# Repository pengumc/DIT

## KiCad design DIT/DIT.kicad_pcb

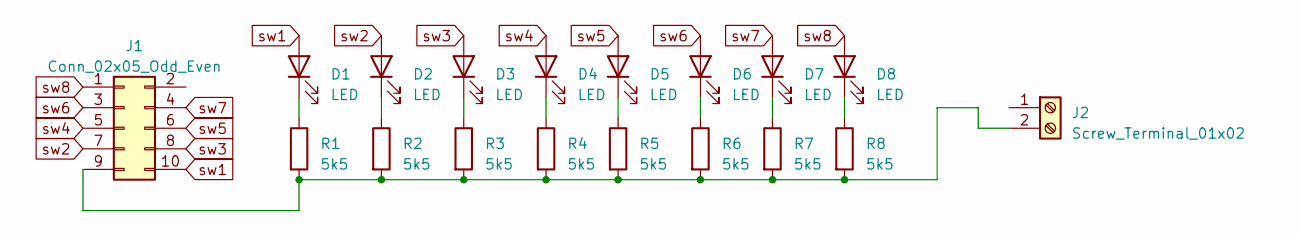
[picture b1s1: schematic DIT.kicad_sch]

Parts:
D1, D2, D3, D4, D5, D6, D7, D8: LED; LED_D3.0mm
J1: Conn_02x05_Odd_Even; PinHeader_2x05_P2.54mm_Vertical
J2: Screw_Terminal_01x02; TerminalBlock_Phoenix_MKDS-1,5-2-5.08_1x02_P5.08mm_Horizont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
R1, R2, R3, R4, R5, R6, R7, R8: 5k5; R_Axial_DIN0207_L6.3mm_D2.5mm_P7.62mm_Horizontal

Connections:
unnamed: D1.1 (K), R1.1
unnamed: D2.1 (K), R2.1
unnamed: D3.1 (K), R3.1
unnamed: D4.1 (K), R4.1
unnamed: D5.1 (K), R5.1
unnamed: D6.1 (K), R6.1
unnamed: D7.1 (K), R7.1
unnamed: D8.1 (K), R8.1
unnamed: J1.9, J2.2, R1.2, R2.2, R3.2, R4.2, R5.2, R6.2, R7.2, R8.2
sw1: D1.2 (A), J1.10
sw2: D2.2 (A), J1.7
sw3: D3.2 (A), J1.8
sw4: D4.2 (A), J1.5
sw5: D5.2 (A), J1.6
sw6: D6.2 (A), J1.3
sw7: D7.2 (A), J1.4
sw8: D8.2 (A), J1.1

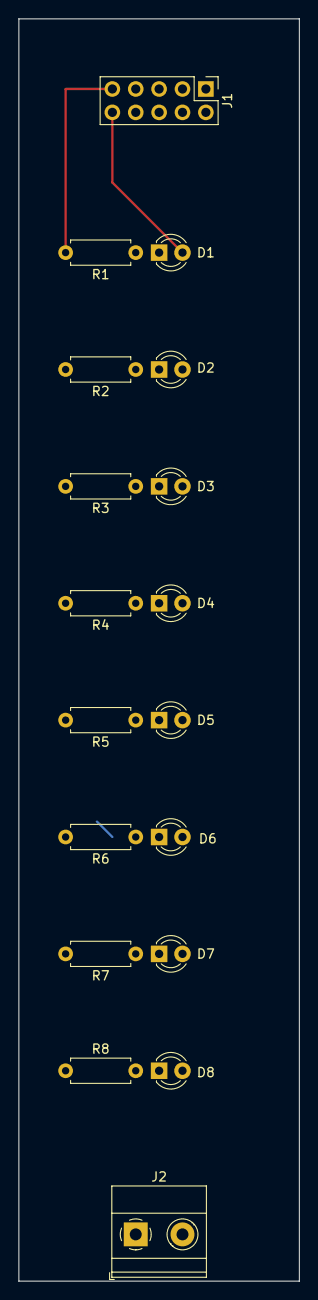
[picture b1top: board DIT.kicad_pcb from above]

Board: 2 copper layers, 30.5 x 137.2 mm, 18 parts (0 on the bottom side), 17 nets.

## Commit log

2023-06-04 Add files
